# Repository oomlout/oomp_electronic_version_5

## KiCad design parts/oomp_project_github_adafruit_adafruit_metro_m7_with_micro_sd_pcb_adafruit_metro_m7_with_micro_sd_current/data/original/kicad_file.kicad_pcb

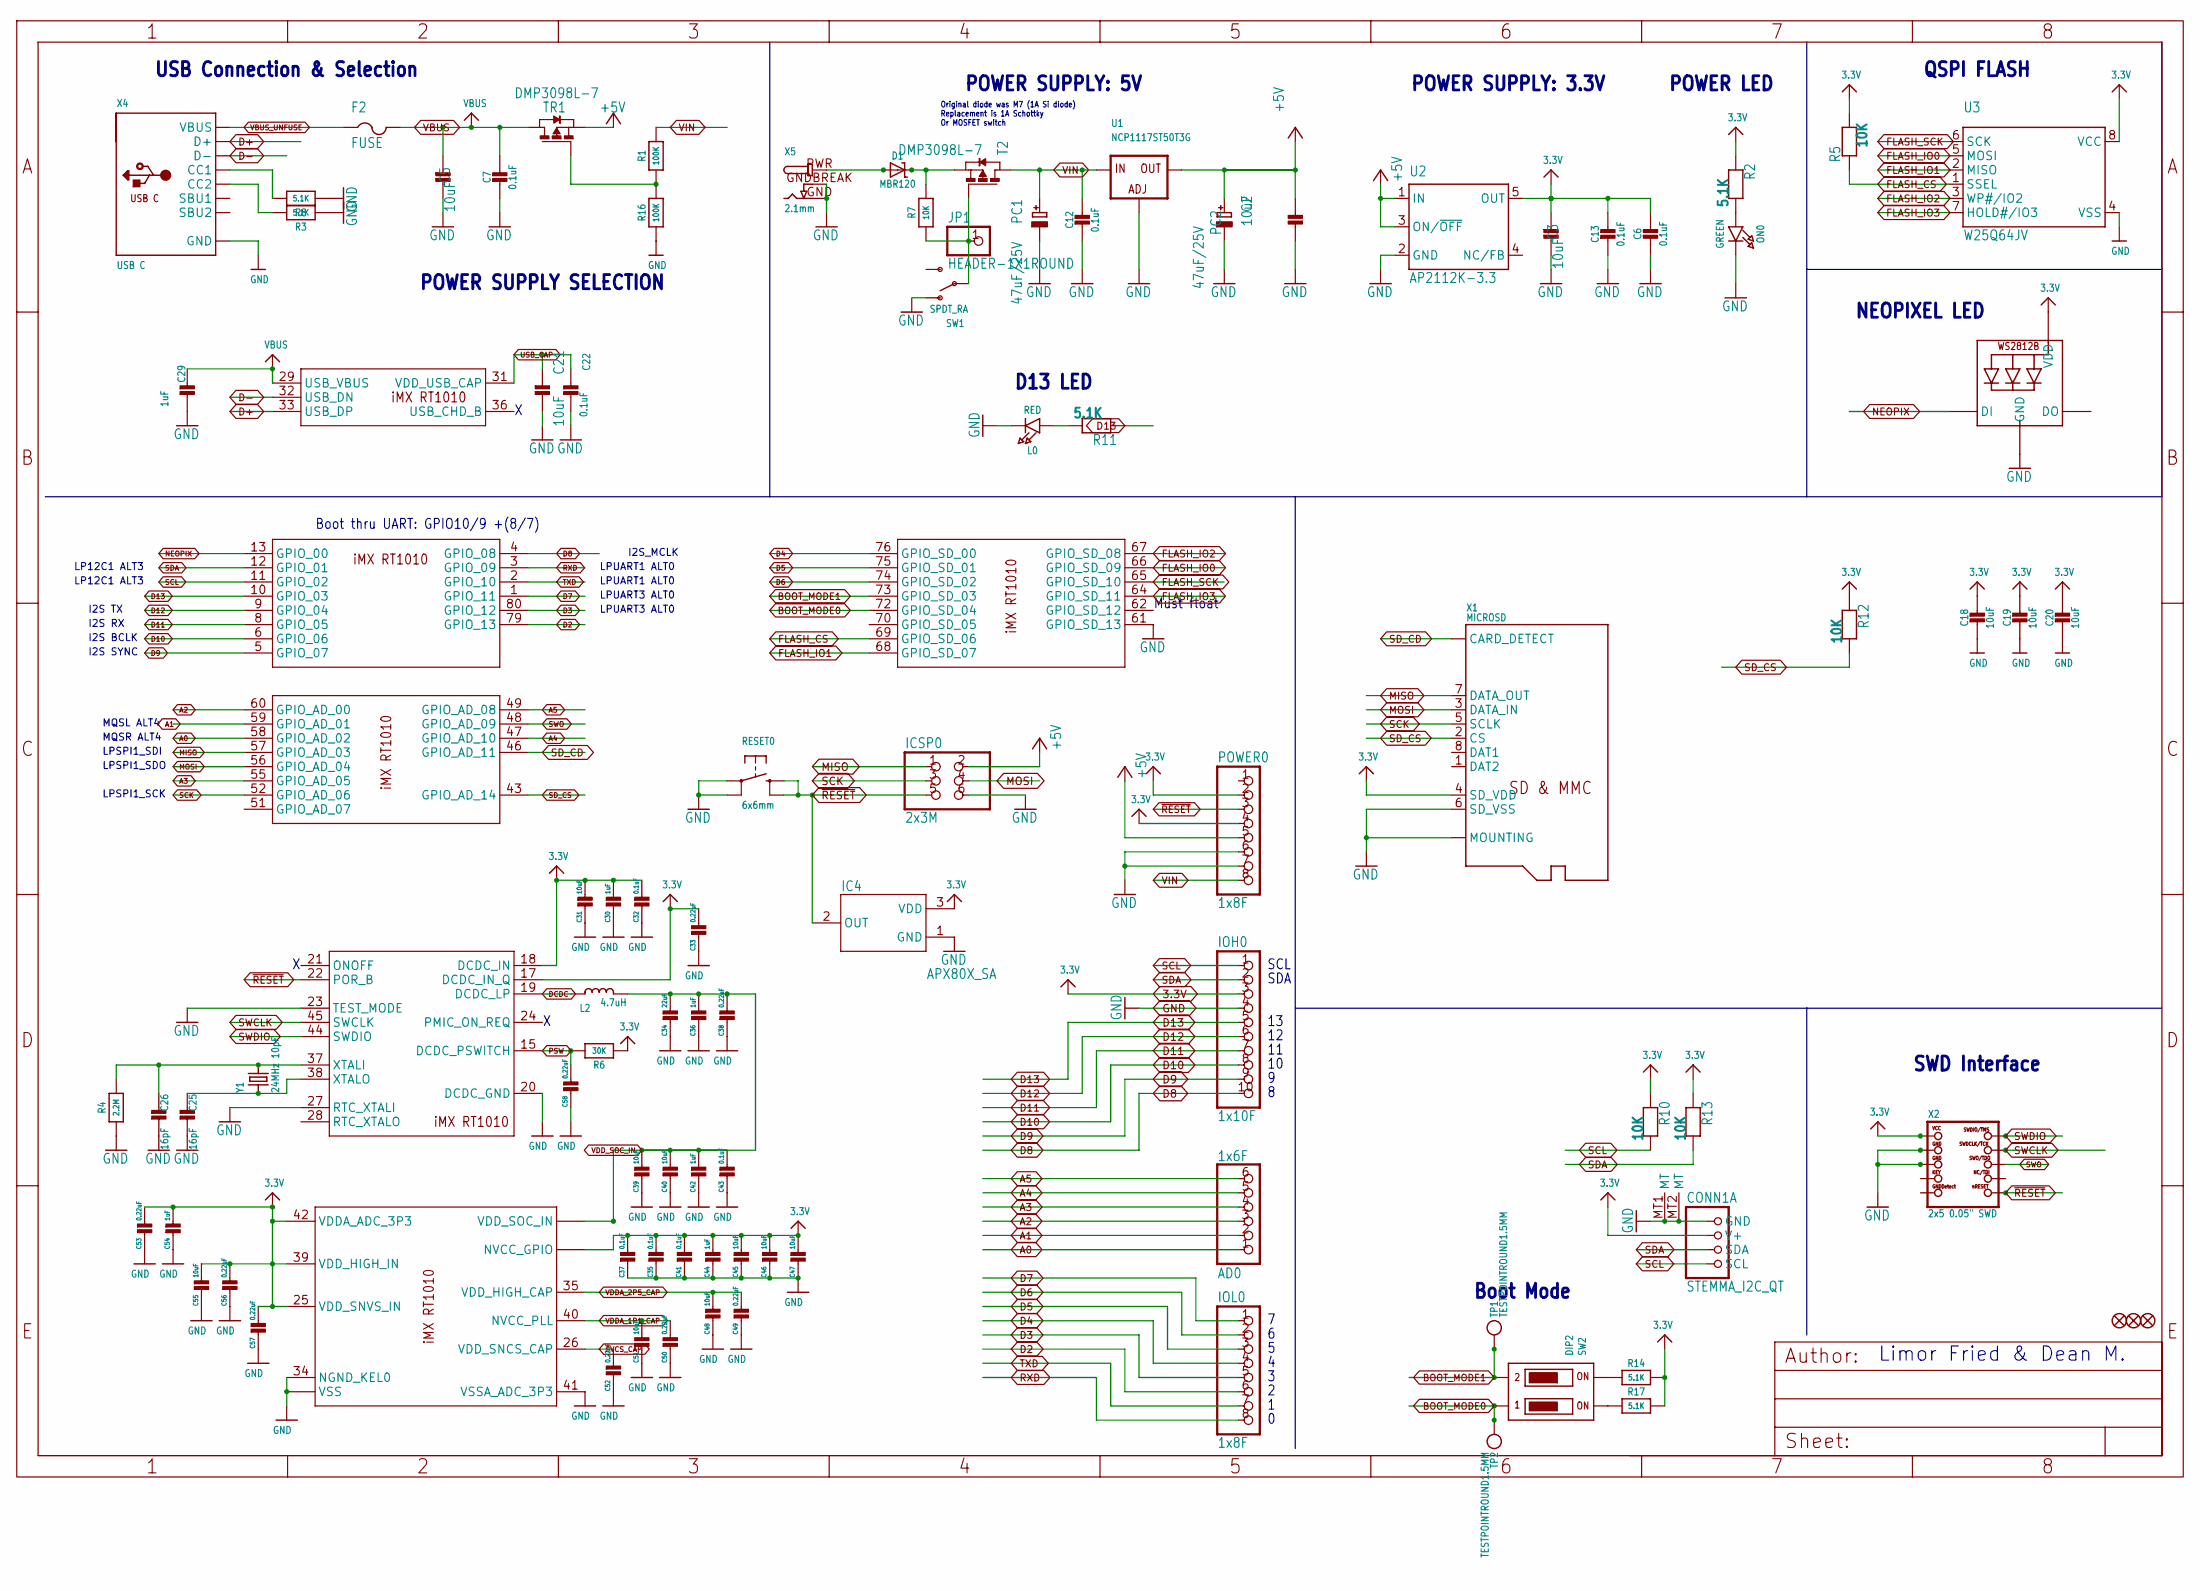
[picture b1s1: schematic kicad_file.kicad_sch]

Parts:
AD0: 1x6F; 1X06_OVALWAVE
C2, C3, C5, C18, C19, C20, C21, C31, C39, C40, C45, C46, C47, C48, C51, C55: 10uF; 0805-NO
C6, C7, C12, C13, C22, C32, C35, C37, C41, C43: 0.1uF; 0603-NO
C25, C26: 16pF; 0603-NO
C29, C30, C36, C42, C44, C54: 1uF; 0603-NO
C33, C38, C49, C50, C52, C53, C56, C57, C58: 0.22uF; 0603-NO
C34: 22uF; 0805-NO
CONN1: STEMMA_I2C_QT; JST_SH4; LCSC C2845363
D1: MBR120; SOD-123
F2: FUSE; R1206
FD1, FD2, FD3: FIDUCIAL_1MM
IC2: IMX_RT1010; QFP50P1400X1400X160-80N
IC4: APX80X_SA; SOT23-WIDE
ICSP0: 2x3M; 2X03_ROUND_70MIL
IOH0: 1x10F; 1X10_OVALWAVE
IOL0: 1x8F; 1X08_OVALWAVE
JP1: HEADER-1X1ROUND; 1X01_ROUND
L0: RED; CHIPLED_0603_NOOUTLINE
L2: 4.7uH; INDUCTOR_1007
LED1: WS2812B_3535FULL; LED3535_FULLPADS
ON0: GREEN; CHIPLED_0603_NOOUTLINE
PC1, PC2: 47uF/25V; PANASONIC_D
POWER0: 1x8F; 1X08_OVALWAVE
R1, R16: 100K; 0603-NO
R2, R3, R8, R11, R14, R17: 5.1K; 0603-NO
R4: 2.2M; 0603-NO
R5, R7, R10, R12, R13: 10K; 0603-NO
R6: 30K; 0603-NO
RESET0: 6x6mm; 6MMX6MM_TACTILE_SMT
SW1: SPDT_RA; SPDT_SMT_SSSS811101
SW2: DIP2; DIPSWITCH_2PIN
T2: DMP3098L-7; SOT-23
TP1, TP2: TESTPOINTROUND1.5MM; TESTPOINT_ROUND_1.5MM
TR1: DMP3098L-7; SOT-23; PART_NUMBER PMV48XP
U1: NCP1117ST50T3G; SOT223-R
U2: AP2112K-3.3; SOT23-DBV
U3: W25Q64JV; SOIC8_208MIL
X1: MICROSD; JLC_ROTATION 90
X2: 2x5 0.05" SWD; 2X05_1.27MM_BOX_POSTS
X4: USB C; USB_C_CUSB31-CFM2AX-01-X; LCSC C165948
X5: 2.1mm; DCJACK_2MM_PTH
Y1: 24MHz 10pF; CRYSTAL_2.5X2

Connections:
3.3V: C3.2, C6.2, C13.1, C18.1, C19.1, C20.1, C30.1, C31.1, C32.1, C33.1, C35.1, C37.1, C41.1, C44.1, C45.1, C46.1, C47.1, C53.1, C54.1, C55.1, C56.1, C57.1, CONN1.2 (V+), IC2.7 (NVCC_GPIO), IC2.17 (DCDC_IN_Q), IC2.18 (DCDC_IN), IC2.25 (VDD_SNVS_IN), IC2.39 (VDD_HIGH_IN), IC2.42 (VDDA_ADC_3P3), IC2.50 (NVCC_GPIO), IC2.63 (NVCC_GPIO), IC2.71 (NVCC_GPIO), IC4.3 (VDD), IOH0.3, LED1.2 (VDD), POWER0.2, POWER0.4, R2.1, R5.2, R6.1, R10.1, R12.1, R13.1, R14.2, R17.2, U2.5 (OUT), U3.8 (VCC), X1.4 (SD_VDD), X2.1 (VCC)
+5V: C2.2, ICSP0.2, PC2.+, POWER0.5, TR1.2 (S), U1.2 (OUT), U1.4 (OUT), U2.1 (IN), U2.3 (ON/~OFF)
A0: AD0.1, IC2.58 (GPIO_AD_02)
A1: AD0.2, IC2.59 (GPIO_AD_01)
A2: AD0.3, IC2.60 (GPIO_AD_00)
A3: AD0.4, IC2.55 (GPIO_AD_05)
A4: AD0.5, IC2.47 (GPIO_AD_10)
A5: AD0.6, IC2.49 (GPIO_AD_08)
BOOT_MODE0: IC2.72 (GPIO_SD_04), SW2.1OFF, TP2.P$1
BOOT_MODE1: IC2.73 (GPIO_SD_03), SW2.2OFF, TP1.P$1
D2: IC2.79 (GPIO_13), IOL0.6
D3: IC2.80 (GPIO_12), IOL0.5
D4: IC2.76 (GPIO_SD_00), IOL0.4
D5: IC2.75 (GPIO_SD_01), IOL0.3
D6: IC2.74 (GPIO_SD_02), IOL0.2
D7: IC2.1 (GPIO_11), IOL0.1
D8: IC2.4 (GPIO_08), IOH0.10
D9: IC2.5 (GPIO_07), IOH0.9
D10: IC2.6 (GPIO_06), IOH0.8
D11: IC2.8 (GPIO_05), IOH0.7
D12: IC2.9 (GPIO_04), IOH0.6
D13: IC2.10 (GPIO_03), IOH0.5, R11.1
D+: IC2.33 (USB_DP), X4.A6 (D+), X4.B6 (D+)
D-: IC2.32 (USB_DN), X4.A7 (D-), X4.B7 (D-)
DCDC: IC2.19 (DCDC_LP), L2.P$1 (1)
FLASH_CS: IC2.69 (GPIO_SD_06), R5.1, U3.1 (SSEL)
FLASH_IO0: IC2.66 (GPIO_SD_09), U3.5 (MOSI)
FLASH_IO1: IC2.68 (GPIO_SD_07), U3.2 (MISO)
FLASH_IO2: IC2.67 (GPIO_SD_08), U3.3 (WP#/IO2)
FLASH_IO3: IC2.64 (GPIO_SD_11), U3.7 (HOLD#/IO3)
FLASH_SCK: IC2.65 (GPIO_SD_10), U3.6 (SCK)
GND: C2.1, C3.1, C5.1, C6.1, C7.2, C12.2, C13.2, C18.2, C19.2, C20.2, C21.1, C22.2, C25.2, C26.2, C29.2, C30.2, C31.2, C32.2, C33.2, C34.2, C35.2, C36.2, C37.2, C38.2, C39.2, C40.2, C41.2, C42.2, C43.2, C44.2, C45.2, C46.2, C47.2, C48.2, C49.2, C50.2, C51.2, C52.2, C53.2, C54.2, C55.2, C56.2, C57.2, C58.2, CONN1.1 (GND), CONN1.MT1 (MT), CONN1.MT2 (MT), IC2.16 (VSS), IC2.20 (DCDC_GND), IC2.23 (TEST_MODE), IC2.27 (RTC_XTALI), IC2.30 (VSS), IC2.34 (NGND_KEL0), IC2.41 (VSSA_ADC_3P3), IC2.54 (VSS), IC2.61 (GPIO_SD_13), IC2.78 (VSS), IC4.1 (GND), ICSP0.6, IOH0.4, L0.C, LED1.4 (GND), ON0.C, PC1.-, PC2.-, POWER0.6, POWER0.7, R3.1, R4.1, R8.1, R16.1, RESET0.A, RESET0.A' (P1), SW1.A (O), U1.1 (ADJ), U2.2 (GND), U3.4 (VSS), X1.6 (SD_VSS), X1.MT1 (MOUNTING), X1.MT2 (MOUNTING), X2.3 (GND), X2.5 (GND), X4.A1B12 (GND), X4.B1A12 (GND), X5.GND, X5.GNDBREAK
MISO: IC2.57 (GPIO_AD_03), ICSP0.1, X1.7 (DATA_OUT)
MOSI: IC2.56 (GPIO_AD_04), ICSP0.4, X1.3 (DATA_IN)
unnamed: L0.A, R11.2
unnamed: ON0.A, R2.2
unnamed: R14.1, SW2.2ON
unnamed: R17.1, SW2.1ON
unnamed: R8.2, X4.A5 (CC1)
unnamed: R3.2, X4.B5 (CC2)
unnamed: C26.1, IC2.37 (XTALI), R4.2, Y1.3 (2)
unnamed: C25.1, IC2.38 (XTALO), Y1.1
unnamed: R1.1, R16.2, TR1.3 (G)
unnamed: D1.C, R7.2, T2.2 (S)
NEOPIX: IC2.13 (GPIO_00), LED1.1 (DI)
PSW: C58.1, IC2.15 (DCDC_PSWITCH), R6.2
PWRIN: D1.A, X5.PWR
PWR_SWITCH: JP1.1, R7.1, SW1.B, T2.3 (G)
RXD: IC2.3 (GPIO_09), IOL0.8
SCK: IC2.52 (GPIO_AD_06), ICSP0.3, X1.5 (SCLK)
SCL: CONN1.4 (SCL), IC2.11 (GPIO_02), IOH0.1, R10.2
SDA: CONN1.3 (SDA), IC2.12 (GPIO_01), IOH0.2, R13.2
SD_CD: IC2.46 (GPIO_AD_11), X1.CD1 (CARD_DETECT), X1.CD2 (CARD_DETECT)
SD_CS: IC2.43 (GPIO_AD_14), R12.2, X1.2 (CS)
SVCS_CAP: C52.1, IC2.26 (VDD_SNCS_CAP)
SWCLK: IC2.45 (SWCLK), X2.4 (SWDCLK)
SWDIO: IC2.44 (SWDIO), X2.2 (SWDIO)
SWO: IC2.48 (GPIO_AD_09), X2.6 (SWO)
TXD: IC2.2 (GPIO_10), IOL0.7
USB_CAP: C21.2, C22.1, IC2.31 (VDD_USB_CAP)
VBUS: C5.2, C7.1, C29.1, F2.2, IC2.29 (USB_VBUS), TR1.1 (D)
VBUS_UNFUSE: F2.1, X4.A4B9 (VBUS), X4.B4A9 (VBUS)
VDDA_1P1_CAP: C50.1, C51.1, IC2.40 (NVCC_PLL)
VDDA_2P5_CAP: C48.1, C49.1, IC2.35 (VDD_HIGH_CAP)
VDD_SOC_IN: C34.1, C36.1, C38.1, C39.1, C40.1, C42.1, C43.1, IC2.14 (VDD_SOC_IN), IC2.53 (VDD_SOC_IN), IC2.77 (VDD_SOC_IN), L2.P$2 (2)
VIN: C12.1, PC1.+, POWER0.8, R1.2, T2.1 (D), U1.3 (IN)
~RESET: IC2.22 (POR_B), IC4.2 (OUT), ICSP0.5, POWER0.3, RESET0.B (S), RESET0.B' (S1), X2.10 (NRESET)

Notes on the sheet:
LPSPI1_SDI
Boot Mode
LPUART3 ALT0
POWER LED
POWER SUPPLY: 5V
LPUART1 ALT0
Boot thru UART: GPIO10/9 +(8/7)
SDA
I2S RX
SCL
POWER SUPPLY SELECTION
LP12C1 ALT3
Original diode was M7 (1A Si diode) Replacement is 1A Schottky Or MOSFET switch
I2S TX
I2S BCLK
SWD Interface
QSPI FLASH
NEOPIXEL LED
MQSL ALT4
USB Connection & Selection
I2S_MCLK
LPSPI1_SDO
Limor Fried & Dean M.
LPSPI1_SCK
Must float
MQSR ALT4
D13 LED
I2S SYNC
POWER SUPPLY: 3.3V

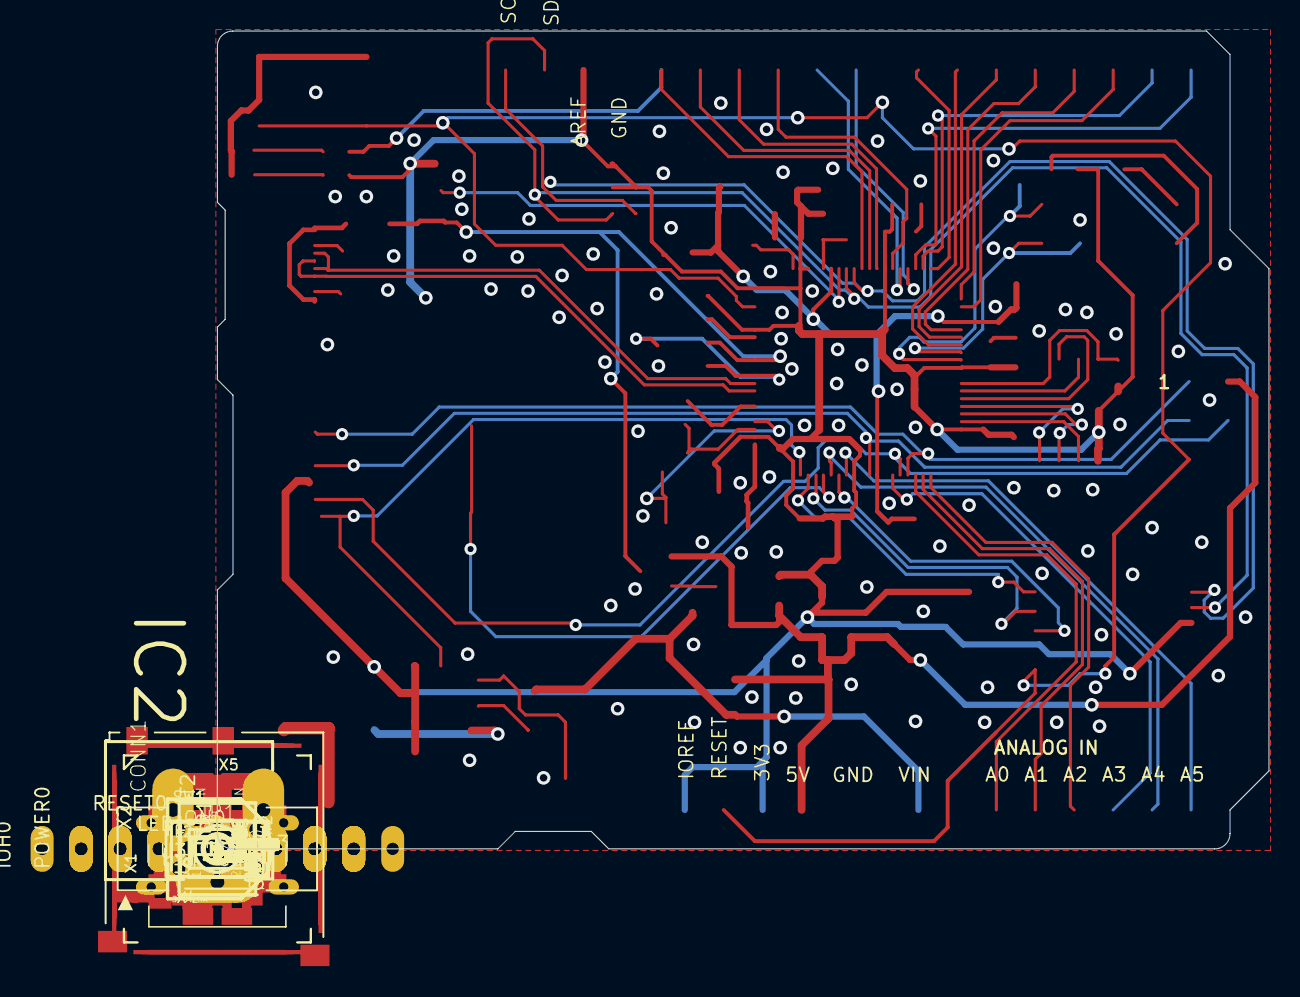
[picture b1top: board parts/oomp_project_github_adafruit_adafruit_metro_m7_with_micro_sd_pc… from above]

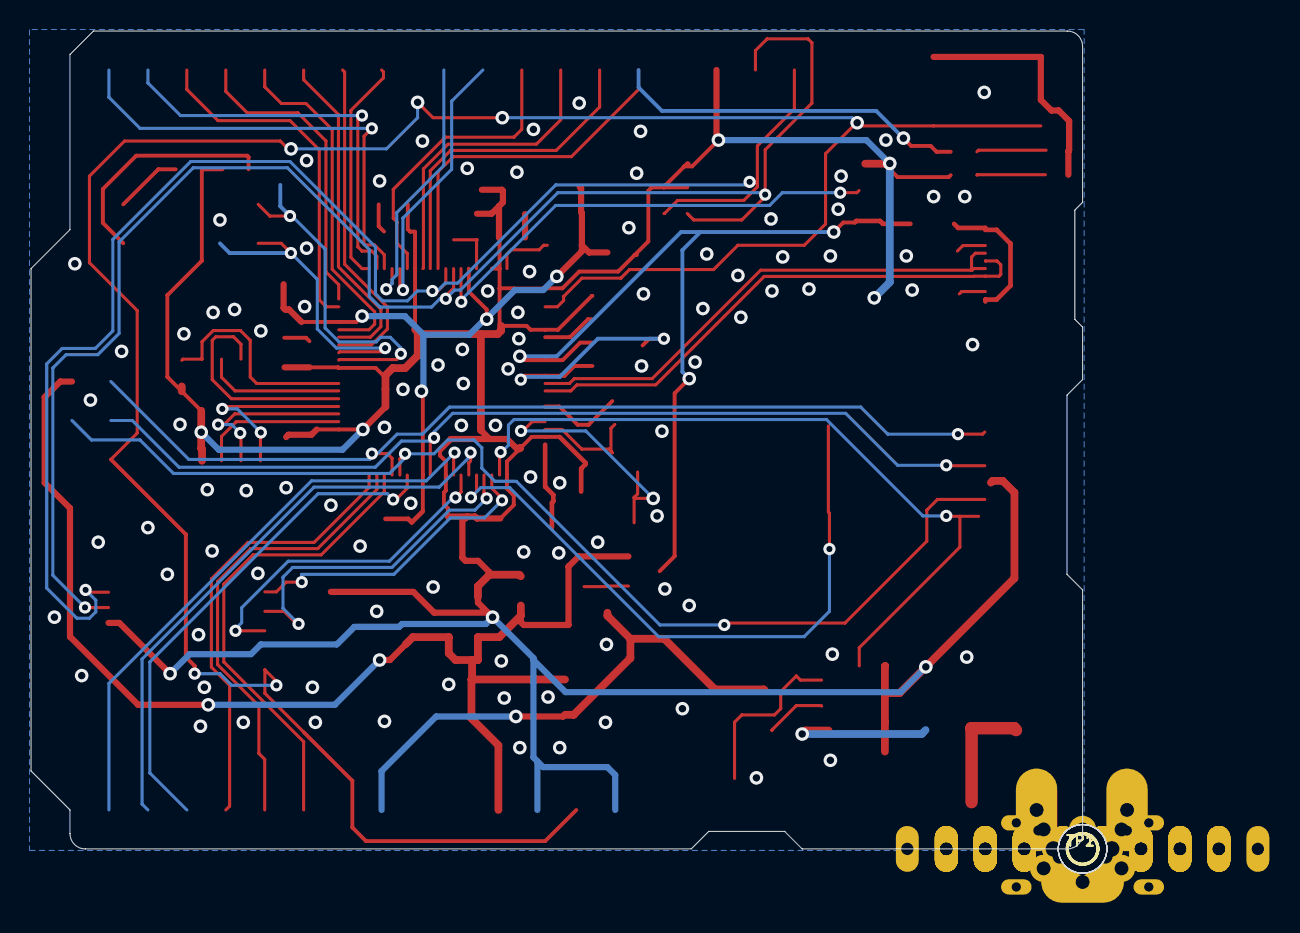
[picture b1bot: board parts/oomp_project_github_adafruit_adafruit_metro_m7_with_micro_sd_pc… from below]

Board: 2 copper layers, 68.6 x 53.3 mm, 101 parts (3 on the bottom side), 67 nets.

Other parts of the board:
U$11: PCBFEAT-REV-040
U$12: M7_RT1011SD_TOP
U$19: M7_RT1011SD_BOT
UNK_HOLE_0: dummyfp0
UNK_HOLE_1: dummyfp1
UNK_HOLE_2: dummyfp2
UNK_HOLE_3: dummyfp3

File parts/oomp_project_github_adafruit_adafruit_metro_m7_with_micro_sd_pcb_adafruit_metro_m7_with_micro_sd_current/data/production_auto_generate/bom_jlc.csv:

Comment,Designator,Footprint,LCSC Part #
,JP1,Adafruit Metro M7 with microSD-import-fps:1X01_ROUND,C7501259
,U$19,Adafruit Metro M7 with microSD-import-fps:M7_RT1011SD_BOT,
,U$12,Adafruit Metro M7 with microSD-import-fps:M7_RT1011SD_TOP,
,U$11,Adafruit Metro M7 with microSD-import-fps:PCBFEAT-REV-040,
,"TP1,TP2",Adafruit Metro M7 with microSD-import-fps:TESTPOINT_ROUND_1.5MM,
0.1uF,"C6,C7,C12,C13,C22,C32,C35,C37,C41,C43",Adafruit Metro M7 with microSD-import-fps:0603-NO,C14663
0.22uF,"C33,C38,C49,C50,C52,C53,C56,C57,C58",Adafruit Metro M7 with microSD-import-fps:0603-NO,
100K,"R1,R16",Adafruit Metro M7 with microSD-import-fps:0603-NO,C25803
10K,"R5,R7,R10,R12,R13",Adafruit Metro M7 with microSD-import-fps:0603-NO,C98220
10uF,"C2,C3,C5,C18,C19,C20,C21,C31,C39,C40,C45,C46,C47,C48,C51,C55",Adafruit Metro M7 with microSD-import-fps:0805-NO,
16pF,"C25,C26",Adafruit Metro M7 with microSD-import-fps:0603-NO,
1uF,"C29,C30,C36,C42,C44,C54",Adafruit Metro M7 with microSD-import-fps:0603-NO,C5673
1x10F,IOH0,Adafruit Metro M7 with microSD-import-fps:1X10_OVALWAVE,C57369
1x6F,AD0,Adafruit Metro M7 with microSD-import-fps:1X06_OVALWAVE,C37208
1x8F,"IOL0,POWER0",Adafruit Metro M7 with microSD-import-fps:1X08_OVALWAVE,C492421
2.1mm,X5,Adafruit Metro M7 with microSD-import-fps:DCJACK_2MM_PTH,
2.2M,R4,Adafruit Metro M7 with microSD-import-fps:0603-NO,C2933170
22uF,C34,Adafruit Metro M7 with microSD-import-fps:0805-NO,
24MHz 10pF,Y1,Adafruit Metro M7 with microSD-import-fps:CRYSTAL_2.5X2,
2x3M,ICSP0,Adafruit Metro M7 with microSD-import-fps:2X03_ROUND_70MIL,
"2x5 0.05"" SWD",X2,Adafruit Metro M7 with microSD-import-fps:2X05_1.27MM_BOX_POSTS,
30K,R6,Adafruit Metro M7 with microSD-import-fps:0603-NO,
4.7uH,L2,Adafruit Metro M7 with microSD-import-fps:INDUCTOR_1007,
47uF/25V,"PC1,PC2",Adafruit Metro M7 with microSD-import-fps:PANASONIC_D,
5.1K,"R2,R3,R8,R11,R14,R17",Adafruit Metro M7 with microSD-import-fps:0603-NO,C23186
6x6mm,RESET0,Adafruit Metro M7 with microSD-import-fps:6MMX6MM_TACTILE_SMT,
AP2112K-3.3,U2,Adafruit Metro M7 with microSD-import-fps:SOT23-DBV,
APX80X_SA,IC4,Adafruit Metro M7 with microSD-import-fps:SOT23-WIDE,
DIP2,SW2,Adafruit Metro M7 with microSD-import-fps:DIPSWITCH_2PIN,
DMP3098L-7,"T2,TR1",Adafruit Metro M7 with microSD-import-fps:SOT-23,
FIDUCIAL_1MM,"FD1,FD2,FD3",Adafruit Metro M7 with microSD-import-fps:FIDUCIAL_1MM,
FUSE,F2,Adafruit Metro M7 with microSD-import-fps:R1206,
GREEN,ON0,Adafruit Metro M7 with microSD-import-fps:CHIPLED_0603_NOOUTLINE,
IMX_RT1010,IC2,Adafruit Metro M7 with microSD-import-fps:QFP50P1400X1400X160-80N,
MBR120,D1,Adafruit Metro M7 with microSD-import-fps:SOD-123,
MICROSD,X1,Adafruit Metro M7 with microSD-import-fps:MICROSD,
NCP1117ST50T3G,U1,Adafruit Metro M7 with microSD-import-fps:SOT223-R,
RED,L0,Adafruit Metro M7 with microSD-import-fps:CHIPLED_0603_NOOUTLINE,
SPDT_RA,SW1,Adafruit Metro M7 with microSD-import-fps:SPDT_SMT_SSSS811101,
STEMMA_I2C_QT,CONN1,Adafruit Metro M7 with microSD-import-fps:JST_SH4,C160404
USB C,X4,Adafruit Metro M7 with microSD-import-fps:USB_C_CUSB31-CFM2AX-01-X,
W25Q64JV,U3,Adafruit Metro M7 with microSD-import-fps:SOIC8_208MIL,
WS2812B_3535FULL,LED1,Adafruit Metro M7 with microSD-import-fps:LED3535_FULLPADS,

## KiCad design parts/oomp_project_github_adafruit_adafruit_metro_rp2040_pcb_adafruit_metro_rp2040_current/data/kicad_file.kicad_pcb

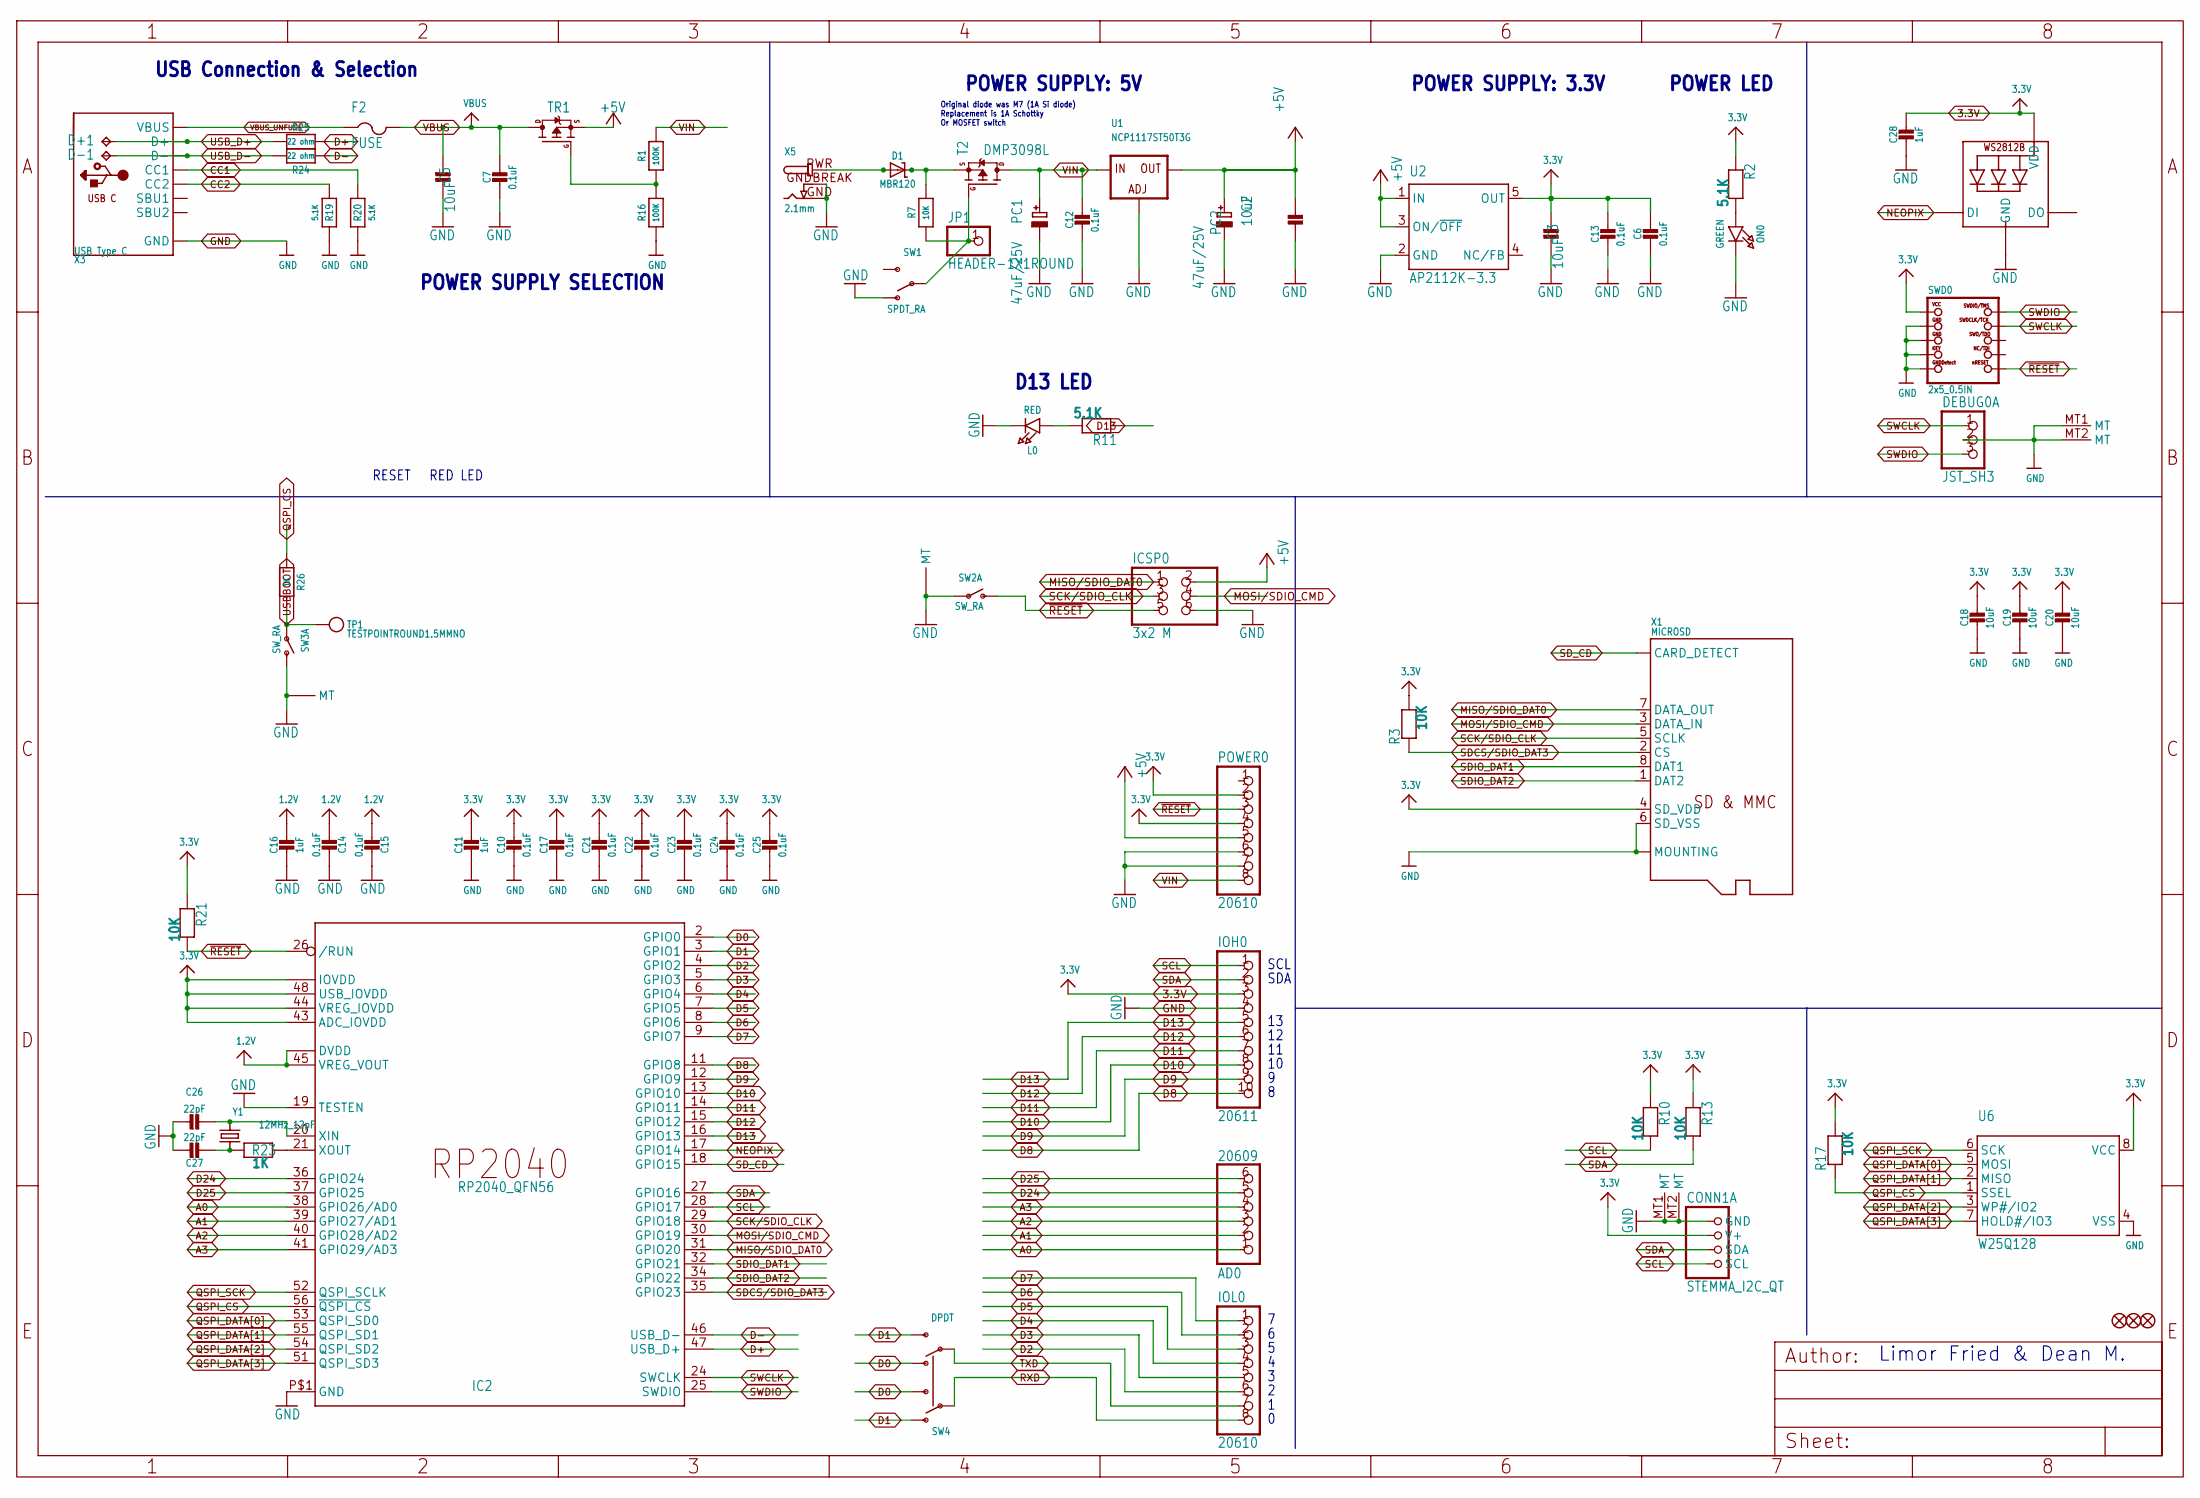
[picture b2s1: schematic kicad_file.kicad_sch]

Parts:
AD0: 20609; 1X06_OVALWAVE
C2, C3, C5, C18, C19, C20: 10uF; 0805-NO
C6, C7, C10, C12, C13, C14, C15, C17, C21, C22, C23, C24, C25: 0.1uF; 0603-NO
C11, C16, C28: 1uF; 0603-NO
C26, C27: 22pF; 0603-NO
CONN1: STEMMA_I2C_QT; JST_SH4; LCSC C2845363
D1: MBR120; SOD-123
D+1: TPB1,27; B1,27
D-1: TPB1,27; B1,27
DEBUG0: JST_SH3
F2: FUSE; R1206
FD1, FD2, FD3: FIDUCIAL_1MM
IC2: RP2040_QFN56; QFN56_7MM_REDUCEDEPAD; LCSC C2040
ICSP0: 3x2 M; 2X03_ROUND_70MIL
IOH0: 20611; 1X10_OVALWAVE
IOL0: 20610; 1X08_OVALWAVE
JP1: HEADER-1X1ROUND; 1X01_ROUND
L0: RED; CHIPLED_0603_NOOUTLINE
LED2: WS2812B_3535FULL; LED3535_FULLPADS
ON0: GREEN; CHIPLED_0603_NOOUTLINE
PC1, PC2: 47uF/25V; PANASONIC_D
POWER0: 20610; 1X08_OVALWAVE
R1, R16: 100K; 0603-NO
R2, R11, R19, R20: 5.1K; 0603-NO
R3, R7, R10, R13, R17, R21: 10K; 0603-NO
R23, R26: 1K; 0603-NO
R24, R25: 22 ohm; 0603-NO
SW1: SPDT_RA; SPDT_SMT_SSSS811101
SW2, SW3: SW_RA; SPST_TACTILE_RA; LCSC C778159
SW4: DPDT; EG1390; LCSC C2837066
SWD0: 2x5_0.5IN; 2X05_1.27MM_BOX_POSTS
T2: DMP3098L; SOT23-WIDE
TP1: TESTPOINTROUND1.5MMNO; TESTPOINT_ROUND_1.5MM_NO
TR1: DMP3098L; SOT23-WIDE
U1: NCP1117ST50T3G; SOT223-R
U2: AP2112K-3.3; SOT23-DBV
U6: W25Q128; SOIC8_208MIL
X1: MICROSD; JLC_ROTATION 90
X3: USB Type C; USB_C_CUSB31-CFM2AX-01-X; LCSC C165948
X5: 2.1mm; DCJACK_2MM_PTH
Y1: 12MHz_12pF; CRYSTAL_2.5X2

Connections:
1.2V: C14.2, C15.2, C16.1, IC2.23 (DVDD), IC2.45 (VREG_VOUT), IC2.50 (DVDD)
3.3V: C3.2, C6.2, C10.1, C11.1, C13.1, C17.1, C18.1, C19.1, C20.1, C21.1, C22.1, C23.1, C24.1, C25.1, C28.1, CONN1.2 (V+), IC2.1 (IOVDD), IC2.10 (IOVDD), IC2.22 (IOVDD), IC2.33 (IOVDD), IC2.42 (IOVDD), IC2.43 (ADC_IOVDD), IC2.44 (VREG_IOVDD), IC2.48 (USB_IOVDD), IC2.49 (IOVDD), IOH0.3, LED2.2 (VDD), POWER0.2, POWER0.4, R2.1, R3.2, R10.1, R13.1, R17.2, R21.1, SWD0.1 (VCC), U2.5 (OUT), U6.8 (VCC), X1.4 (SD_VDD)
+5V: C2.2, ICSP0.2, PC2.+, POWER0.5, TR1.2 (S), U1.2 (OUT), U1.4 (OUT), U2.1 (IN), U2.3 (ON/~OFF)
A0: AD0.1, IC2.38 (GPIO26/AD0)
A1: AD0.2, IC2.39 (GPIO27/AD1)
A2: AD0.3, IC2.40 (GPIO28/AD2)
A3: AD0.4, IC2.41 (GPIO29/AD3)
CC1: R20.2, X3.A5 (CC1)
CC2: R19.2, X3.B5 (CC2)
D0: IC2.2 (GPIO0), SW4.O2, SW4.S1
D1: IC2.3 (GPIO1), SW4.O1, SW4.S2
D2: IC2.4 (GPIO2), IOL0.6
D3: IC2.5 (GPIO3), IOL0.5
D4: IC2.6 (GPIO4), IOL0.4
D5: IC2.7 (GPIO5), IOL0.3
D6: IC2.8 (GPIO6), IOL0.2
D7: IC2.9 (GPIO7), IOL0.1
D8: IC2.11 (GPIO8), IOH0.10
D9: IC2.12 (GPIO9), IOH0.9
D10: IC2.13 (GPIO10), IOH0.8
D11: IC2.14 (GPIO11), IOH0.7
D12: IC2.15 (GPIO12), IOH0.6
D13: IC2.16 (GPIO13), IOH0.5, R11.1
D24: AD0.5, IC2.36 (GPIO24)
D25: AD0.6, IC2.37 (GPIO25)
D+: IC2.47 (USB_D+), R25.2
D-: IC2.46 (USB_D-), R24.2
GND: C2.1, C3.1, C5.1, C6.1, C7.2, C10.2, C11.2, C12.2, C13.2, C14.1, C15.1, C16.2, C17.2, C18.2, C19.2, C20.2, C21.2, C22.2, C23.2, C24.2, C25.2, C26.1, C27.1, C28.2, CONN1.1 (GND), CONN1.MT1 (MT), CONN1.MT2 (MT), DEBUG0.2, DEBUG0.MT1 (MT), DEBUG0.MT2 (MT), IC2.19 (TESTEN), IC2.P$1 (GND), ICSP0.6, IOH0.4, L0.C, LED2.4 (GND), ON0.C, PC1.-, PC2.-, POWER0.6, POWER0.7, R16.1, R19.1, R20.1, SW1.A (O), SW2.1, SW2.MT1 (MT), SW2.MT2 (MT), SW3.2 (S), SW3.MT1 (MT), SW3.MT2 (MT), SWD0.3 (GND), SWD0.5 (GND), SWD0.7 (KEY), SWD0.9 (GNDDETECT), U1.1 (ADJ), U2.2 (GND), U6.4 (VSS), X1.6 (SD_VSS), X1.MT1 (MOUNTING), X1.MT2 (MOUNTING), X3.A1B12 (GND), X3.B1A12 (GND), X5.GND, X5.GNDBREAK
MISO/SDIO_DAT0: IC2.31 (GPIO20), ICSP0.1, X1.7 (DATA_OUT)
MOSI/SDIO_CMD: IC2.30 (GPIO19), ICSP0.4, X1.3 (DATA_IN)
unnamed: L0.A, R11.2
unnamed: ON0.A, R2.2
unnamed: C26.2, IC2.20 (XIN), Y1.3 (2)
unnamed: C27.2, R23.1, Y1.1
unnamed: R1.1, R16.2, TR1.1 (G)
unnamed: IC2.21 (XOUT), R23.2
unnamed: D1.C, R7.2, T2.2 (S)
NEOPIX: IC2.17 (GPIO14), LED2.1 (DI)
PWRIN: D1.A, X5.PWR
PWR_SWITCH: JP1.1, R7.1, SW1.B, T2.1 (G)
QSPI_CS: IC2.56 (~QSPI_CS), R17.1, R26.1, U6.1 (SSEL)
QSPI_DATA[0]: IC2.53 (QSPI_SD0), U6.5 (MOSI)
QSPI_DATA[1]: IC2.55 (QSPI_SD1), U6.2 (MISO)
QSPI_DATA[2]: IC2.54 (QSPI_SD2), U6.3 (WP#/IO2)
QSPI_DATA[3]: IC2.51 (QSPI_SD3), U6.7 (HOLD#/IO3)
QSPI_SCK: IC2.52 (QSPI_SCLK), U6.6 (SCK)
RXD: IOL0.8, SW4.P1
SCK/SDIO_CLK: IC2.29 (GPIO18), ICSP0.3, X1.5 (SCLK)
SCL: CONN1.4 (SCL), IC2.28 (GPIO17), IOH0.1, R10.2
SDA: CONN1.3 (SDA), IC2.27 (GPIO16), IOH0.2, R13.2
SDCS/SDIO_DAT3: IC2.35 (GPIO23), R3.1, X1.2 (CS)
SDIO_DAT1: IC2.32 (GPIO21), X1.8 (DAT1)
SDIO_DAT2: IC2.34 (GPIO22), X1.1 (DAT2)
SD_CD: IC2.18 (GPIO15), X1.CD1 (CARD_DETECT), X1.CD2 (CARD_DETECT)
SWCLK: DEBUG0.1, IC2.24 (SWCLK), SWD0.4 (SWDCLK)
SWDIO: DEBUG0.3, IC2.25 (SWDIO), SWD0.2 (SWDIO)
TXD: IOL0.7, SW4.P2
USBBOOT: R26.2, SW3.1, TP1.P$1
USB_D+: D+1.TP, R25.1, X3.A6 (D+), X3.B6 (D+)
USB_D-: D-1.TP, R24.1, X3.A7 (D-), X3.B7 (D-)
VBUS: C5.2, C7.1, F2.2, TR1.3 (D)
VBUS_UNFUSE: F2.1, X3.A4B9 (VBUS), X3.B4A9 (VBUS)
VIN: C12.1, PC1.+, POWER0.8, R1.2, T2.3 (D), U1.3 (IN)
~RESET: IC2.26 (/RUN), ICSP0.5, POWER0.3, R21.2, SW2.2 (S), SWD0.10 (NRESET)

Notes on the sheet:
D13 LED
RESET
SCL
SDA
POWER LED
POWER SUPPLY: 5V
Limor Fried & Dean M.
POWER SUPPLY: 3.3V
POWER SUPPLY SELECTION
USB Connection & Selection
RED LED
Original diode was M7 (1A Si diode) Replacement is 1A Schottky Or MOSFET switch

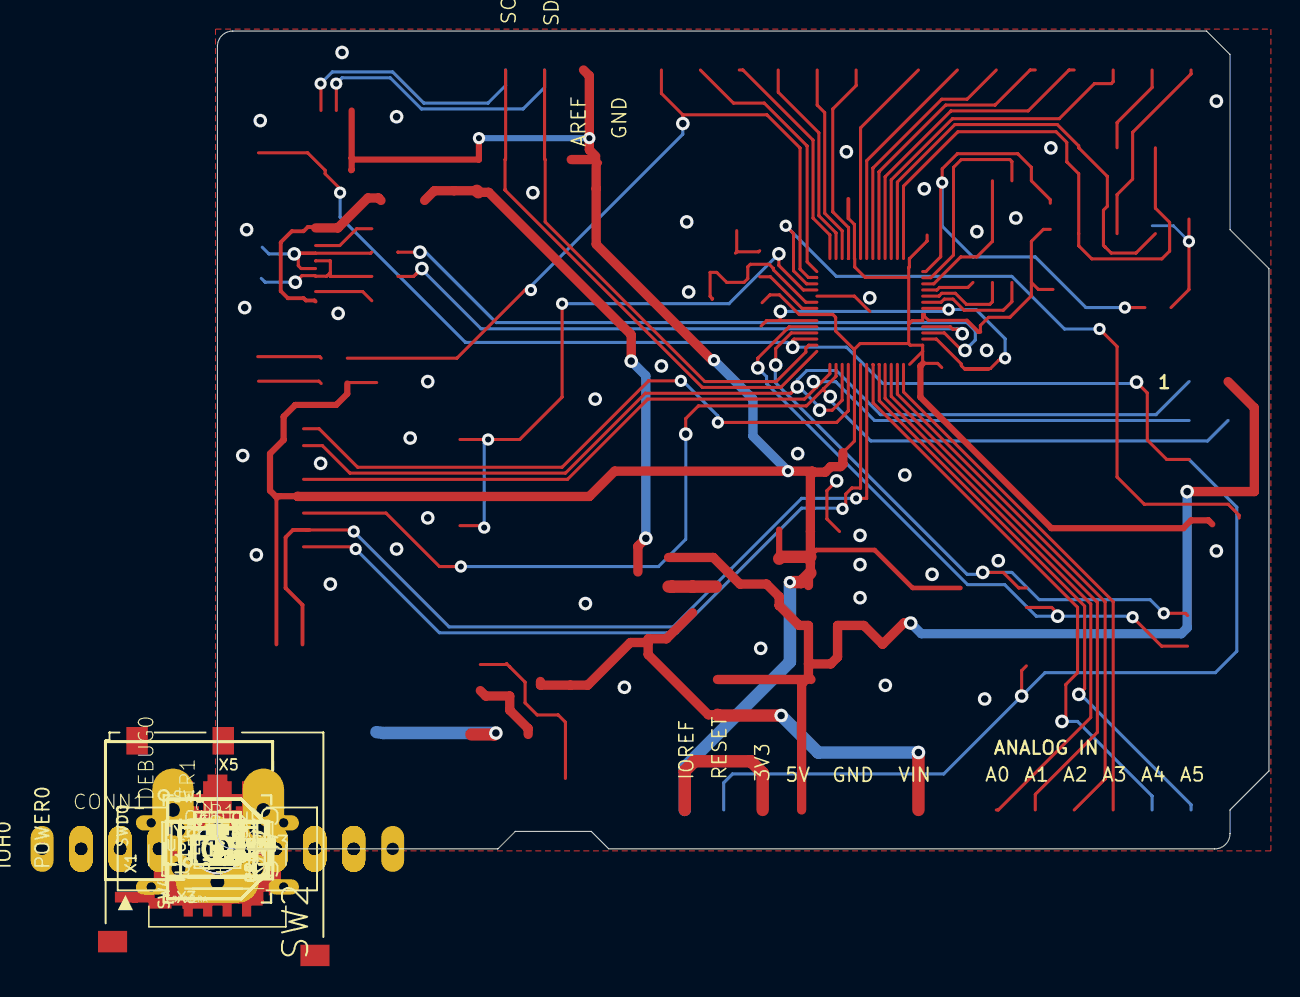
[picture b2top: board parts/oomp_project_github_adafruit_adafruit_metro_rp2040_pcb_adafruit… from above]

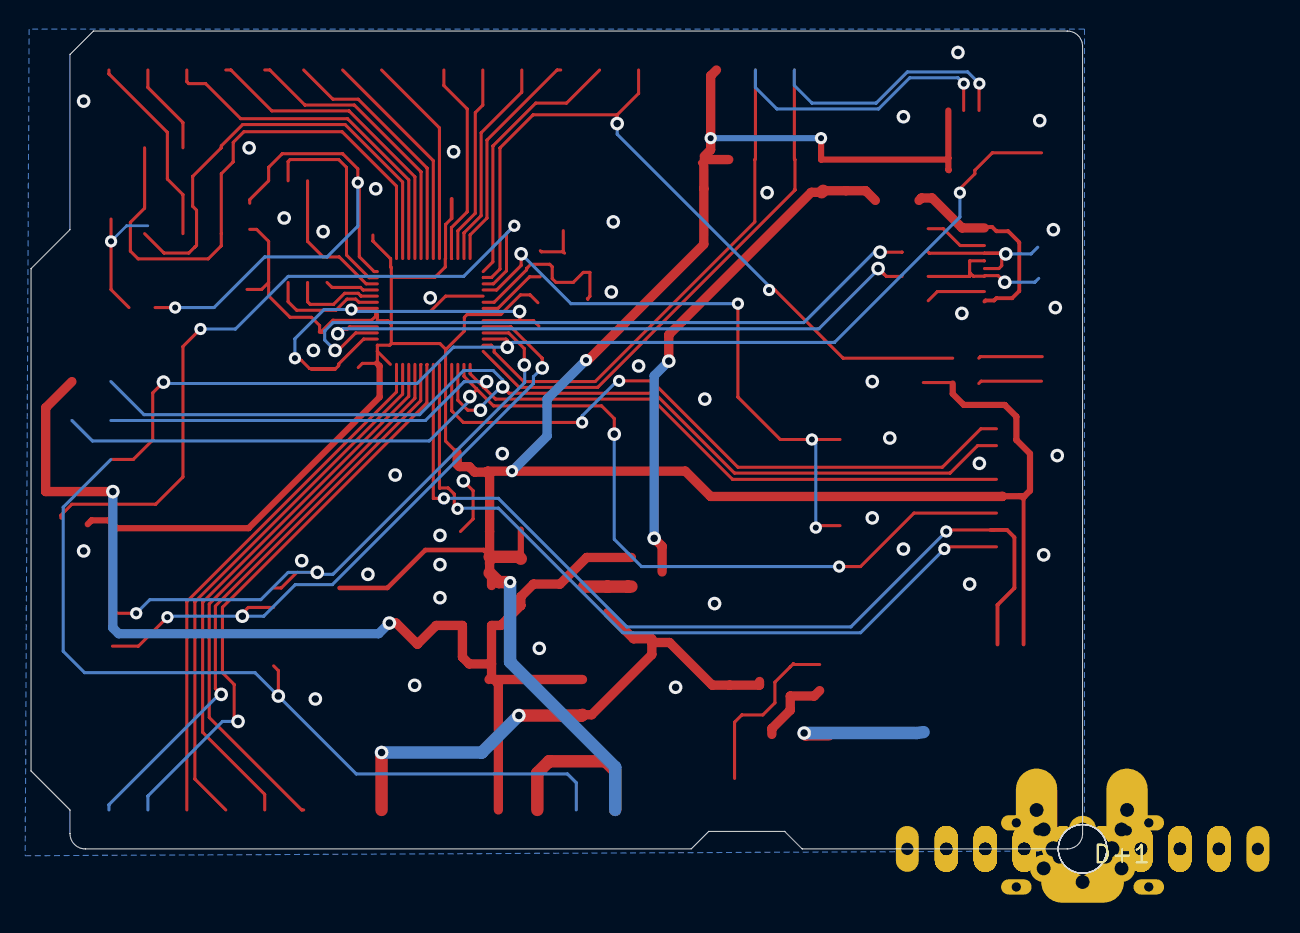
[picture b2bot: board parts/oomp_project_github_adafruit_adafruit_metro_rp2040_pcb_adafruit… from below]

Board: 2 copper layers, 68.6 x 53.3 mm, 83 parts (4 on the bottom side), 64 nets.

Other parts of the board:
U$11: PCBFEAT-REV-040
U$15: METRO_RP2040_BOT
U$29: METRO_RP2040_TOP
UNK_HOLE_0: dummyfp0
UNK_HOLE_1: dummyfp1
UNK_HOLE_2: dummyfp2
UNK_HOLE_3: dummyfp3

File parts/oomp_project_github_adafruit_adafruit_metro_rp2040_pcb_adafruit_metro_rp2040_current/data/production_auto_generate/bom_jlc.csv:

Comment,Designator,Footprint,LCSC Part #
,JP1,Adafruit Metro RP2040-import-fps:1X01_ROUND,C7501259
,U$15,Adafruit Metro RP2040-import-fps:METRO_RP2040_BOT,
,U$29,Adafruit Metro RP2040-import-fps:METRO_RP2040_TOP,
,U$11,Adafruit Metro RP2040-import-fps:PCBFEAT-REV-040,
,TP1,Adafruit Metro RP2040-import-fps:TESTPOINT_ROUND_1.5MM_NO,
0.1uF,"C6,C7,C10,C12,C13,C14,C15,C17,C21,C22,C23,C24,C25",Adafruit Metro RP2040-import-fps:0603-NO,C14663
100K,"R1,R16",Adafruit Metro RP2040-import-fps:0603-NO,C25803
10K,"R3,R7,R10,R13,R17,R21",Adafruit Metro RP2040-import-fps:0603-NO,C98220
10uF,"C2,C3,C5,C18,C19,C20",Adafruit Metro RP2040-import-fps:0805-NO,
12MHz_12pF,Y1,Adafruit Metro RP2040-import-fps:CRYSTAL_2.5X2,
1K,"R23,R26",Adafruit Metro RP2040-import-fps:0603-NO,C2907002
1uF,"C11,C16,C28",Adafruit Metro RP2040-import-fps:0603-NO,C5673
2.1mm,X5,Adafruit Metro RP2040-import-fps:DCJACK_2MM_PTH,
20609,AD0,Adafruit Metro RP2040-import-fps:1X06_OVALWAVE,C37208
20610,"IOL0,POWER0",Adafruit Metro RP2040-import-fps:1X08_OVALWAVE,C492421
20611,IOH0,Adafruit Metro RP2040-import-fps:1X10_OVALWAVE,C57369
22 ohm,"R24,R25",Adafruit Metro RP2040-import-fps:0603-NO,C23345
22pF,"C26,C27",Adafruit Metro RP2040-import-fps:0603-NO,C105620
2x5_0.5IN,SWD0,Adafruit Metro RP2040-import-fps:2X05_1.27MM_BOX_POSTS,
3x2 M,ICSP0,Adafruit Metro RP2040-import-fps:2X03_ROUND_70MIL,
47uF/25V,"PC1,PC2",Adafruit Metro RP2040-import-fps:PANASONIC_D,
5.1K,"R2,R11,R19,R20",Adafruit Metro RP2040-import-fps:0603-NO,C23186
AP2112K-3.3,U2,Adafruit Metro RP2040-import-fps:SOT23-DBV,
DMP3098L,"T2,TR1",Adafruit Metro RP2040-import-fps:SOT23-WIDE,
DPDT,SW4,Adafruit Metro RP2040-import-fps:EG1390,
FIDUCIAL_1MM,"FD1,FD2,FD3",Adafruit Metro RP2040-import-fps:FIDUCIAL_1MM,
FUSE,F2,Adafruit Metro RP2040-import-fps:R1206,
GREEN,ON0,Adafruit Metro RP2040-import-fps:CHIPLED_0603_NOOUTLINE,
JST_SH3,DEBUG0,Adafruit Metro RP2040-import-fps:JST_SH3,
MBR120,D1,Adafruit Metro RP2040-import-fps:SOD-123,
MICROSD,X1,Adafruit Metro RP2040-import-fps:MICROSD,
NCP1117ST50T3G,U1,Adafruit Metro RP2040-import-fps:SOT223-R,
RED,L0,Adafruit Metro RP2040-import-fps:CHIPLED_0603_NOOUTLINE,
RP2040_QFN56,IC2,Adafruit Metro RP2040-import-fps:QFN56_7MM_REDUCEDEPAD,
SPDT_RA,SW1,Adafruit Metro RP2040-import-fps:SPDT_SMT_SSSS811101,
STEMMA_I2C_QT,CONN1,Adafruit Metro RP2040-import-fps:JST_SH4,C160404
SW_RA,"SW2,SW3",Adafruit Metro RP2040-import-fps:SPST_TACTILE_RA,
"TPB1,27","D+1,D-1","Adafruit Metro RP2040-import-fps:B1,27",
USB Type C,X3,Adafruit Metro RP2040-import-fps:USB_C_CUSB31-CFM2AX-01-X,
W25Q128,U6,Adafruit Metro RP2040-import-fps:SOIC8_208MIL,
WS2812B_3535FULL,LED2,Adafruit Metro RP2040-import-fps:LED3535_FULLPADS,
